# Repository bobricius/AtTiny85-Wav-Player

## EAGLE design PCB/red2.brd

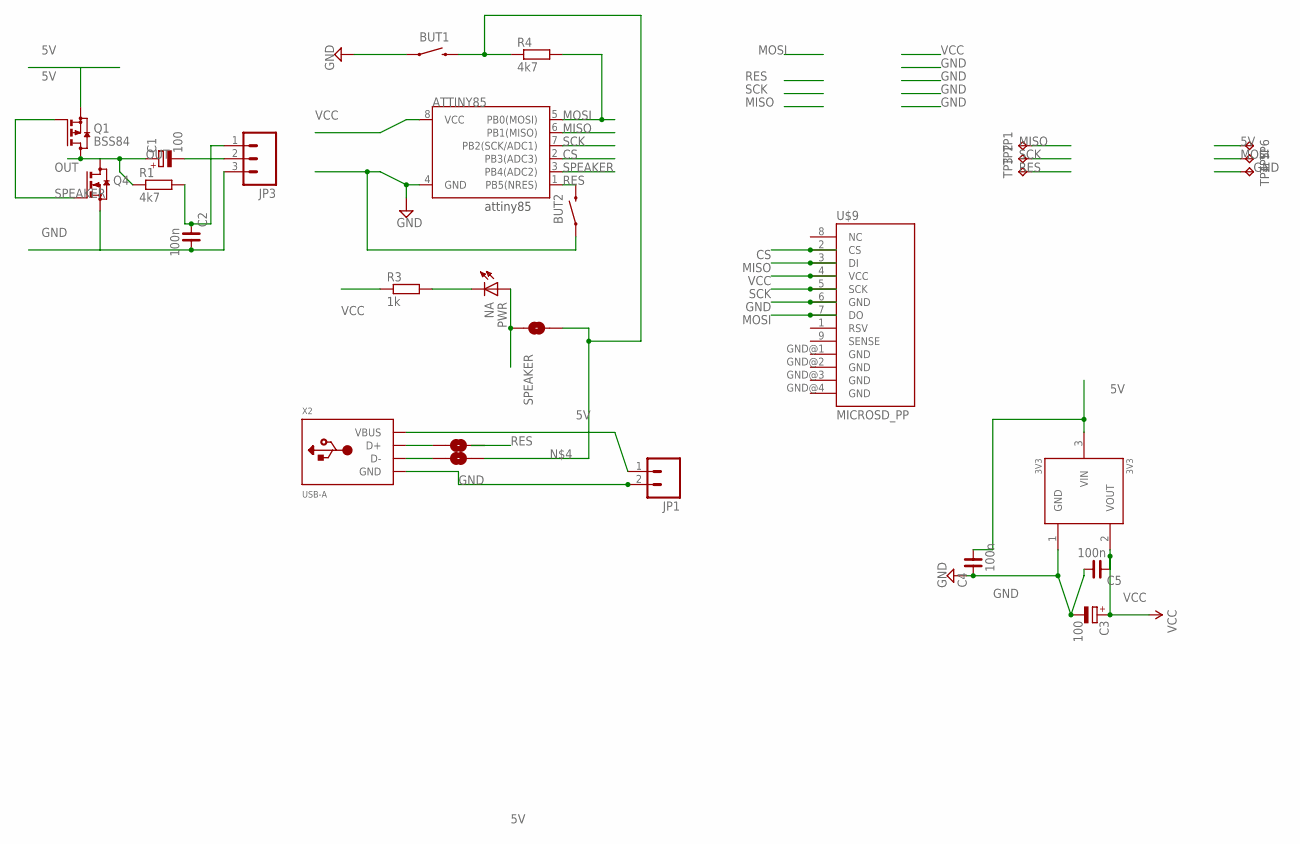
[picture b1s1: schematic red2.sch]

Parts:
3V3: 3V3; SOT23
ATTINY85: ATTINY45; SO08-EIAJ
BUT1, BUT2: SWITCH-MOMENTARY-2-SMD-1101NE; TACTILE-SWITCH-1101NE
C1, C3: 100; 153CLV-0605
C2, C4, C5: 100n; C0603
JP1: M02PTH; 1X02
JP3: M03PTH; 1X03
PWR: NA; LED-0603
Q1: BSS84; SOT23
Q4: BSS123; SOT23
R1, R4: 4k7; R0603
R3: 1k; R0603
SJ1, SJ2, SJ3: SOLDERJUMPERNC; SJ_2S
TP1, TP2, TP3, TP4, TP5, TP6: TPB1,27; B1,27
U$9: MICROSD_PP
X2: USB-A; MOLEX_480371000

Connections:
5V: 3V3.3 (VIN), C4.1, JP1.1, Q1.2 (S), TP6.TP, X2.1 (VBUS)
CS: ATTINY85.2 (PB3(ADC3)), U$9.2 (CS)
GND: 3V3.1 (GND), ATTINY85.4 (GND), BUT1.P$1 (1), BUT2.P$1 (1), C2.1, C3.-, C4.2, C5.1, JP1.2, JP3.3, Q4.2 (S), TP4.TP, U$9.6 (GND), X2.4 (GND)
MISO: ATTINY85.6 (PB1(MISO)), TP1.TP, U$9.3 (DI)
MOSI: ATTINY85.5 (PB0(MOSI)), R4.2, TP5.TP, U$9.7 (DO)
unnamed: PWR.C, R3.2
unnamed: C1.-, JP3.2
unnamed: SJ3.1, X2.2 (D-)
unnamed: BUT1.P$2 (2), R4.1, SJ1.2, SJ3.2
unnamed: SJ2.1, X2.3 (D+)
unnamed: C2.2, JP3.1, R1.2
OUT: C1.+, Q1.3 (D), Q4.3 (D), R1.1
RES: ATTINY85.1 (PB5(NRES)), BUT2.P$2 (2), TP3.TP
SCK: ATTINY85.7 (PB2(SCK/ADC1)), TP2.TP, U$9.5 (SCK)
SPEAKER: ATTINY85.3 (PB4(ADC2)), PWR.A, Q1.1 (G), Q4.1 (G), SJ1.1
VCC: 3V3.2 (VOUT), ATTINY85.8 (VCC), C3.+, C5.2, R3.1, U$9.4 (VCC)

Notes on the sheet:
attiny85

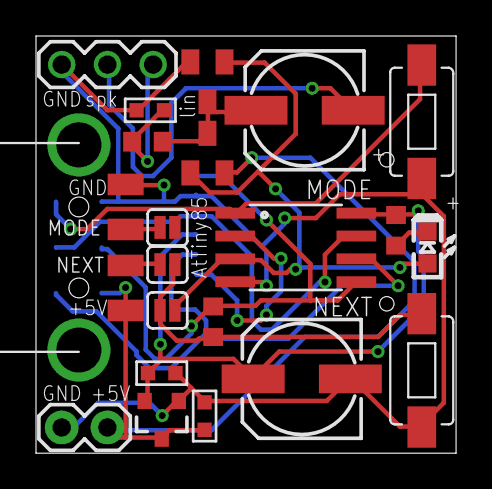
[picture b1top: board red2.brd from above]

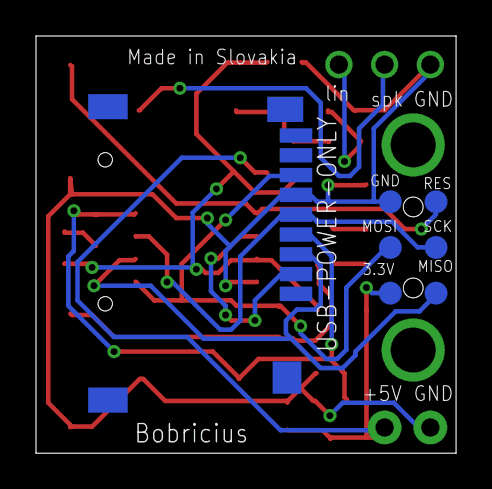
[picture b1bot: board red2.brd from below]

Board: 2 copper layers, 23.3 x 23.2 mm, 28 parts (7 on the bottom side), 16 nets.

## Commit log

2014-11-12 :octocat: Added .gitattributes & .gitignore files
2014-11-12 first upload
